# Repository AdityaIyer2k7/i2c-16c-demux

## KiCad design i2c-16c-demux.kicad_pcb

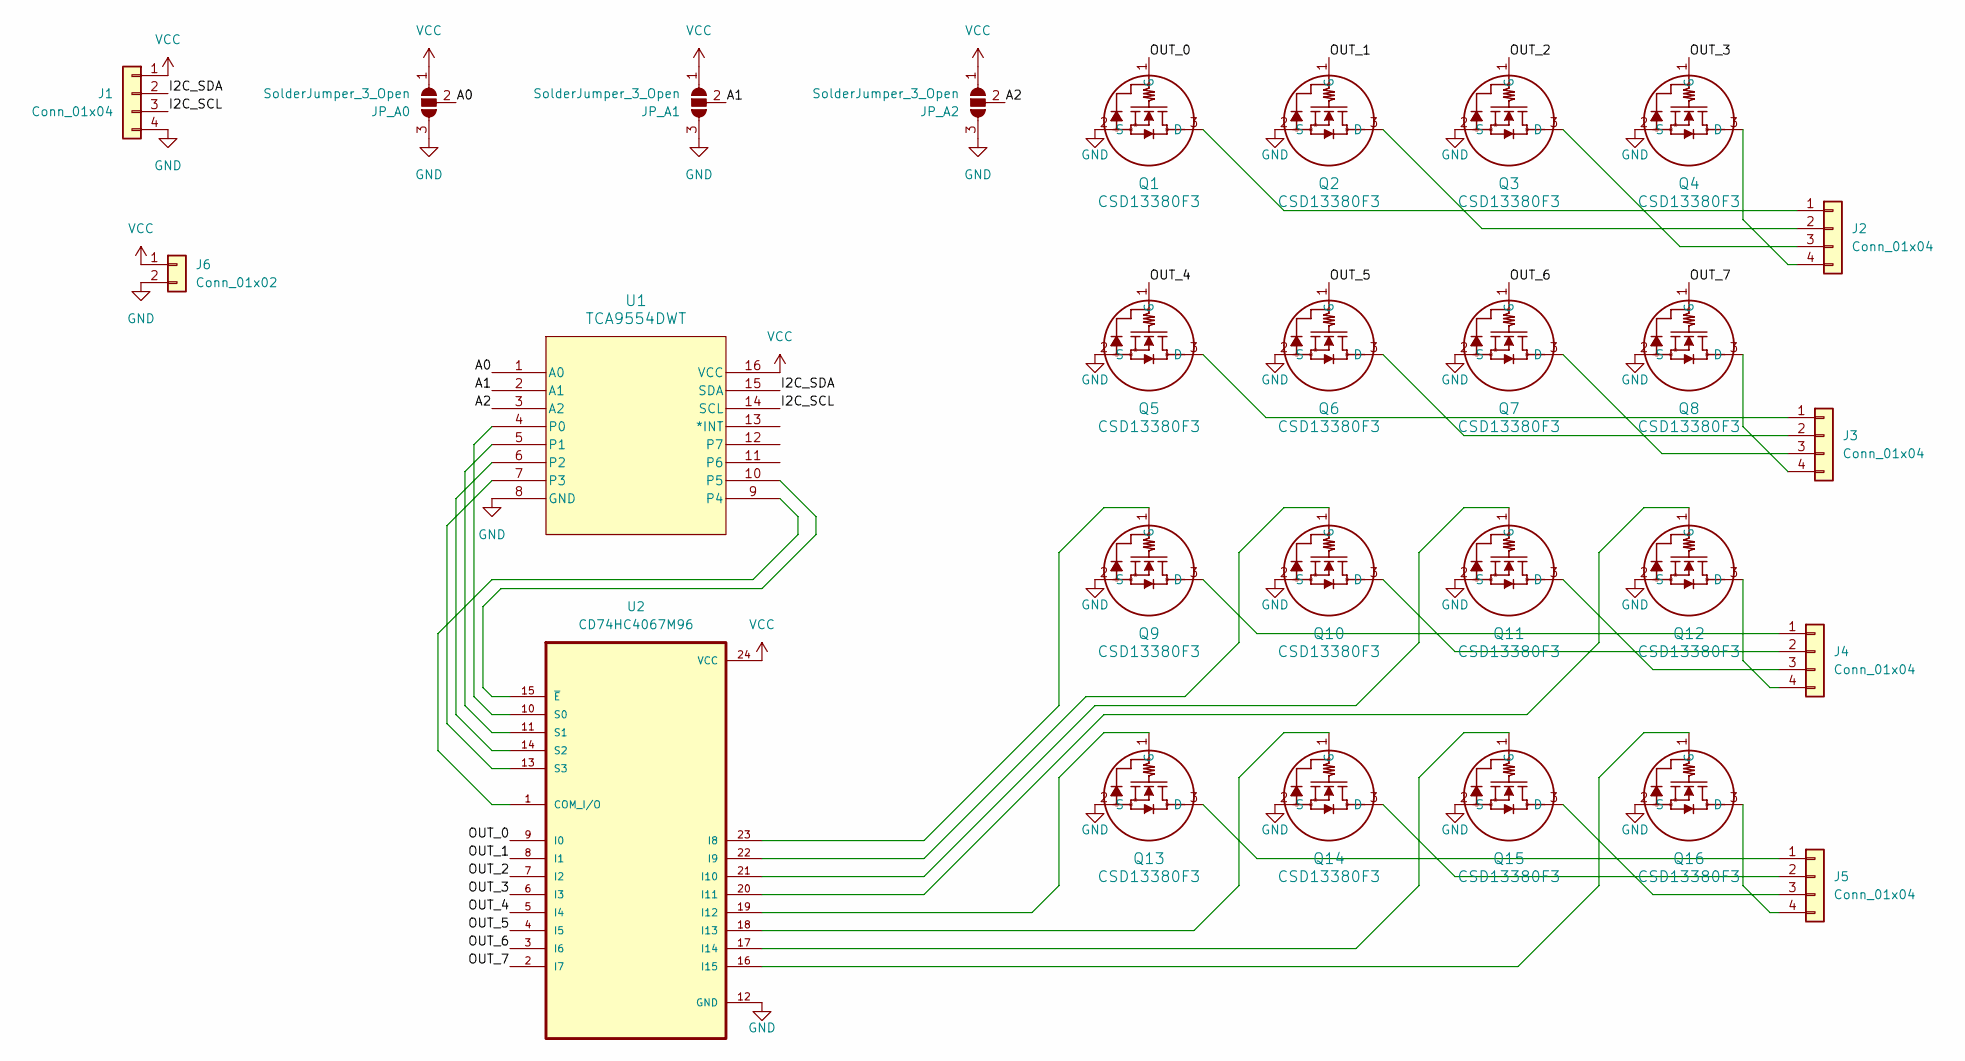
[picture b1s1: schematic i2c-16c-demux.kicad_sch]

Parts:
J1, J2, J3, J4, J5: Conn_01x04; PinSocket_1x04_P2.54mm_Vertical
J6: Conn_01x02; PinSocket_1x02_P2.54mm_Vertical
JP_A0, JP_A1, JP_A2: SolderJumper_3_Open; SolderJumper-3_P2.0mm_Open_TrianglePad1.0x1.5mm
Q1, Q2, Q3, Q4, Q5, Q6, Q7, Q8, Q9, Q10, Q11, Q12, Q13, Q14, Q15, Q16: CSD13380F3; SC59_DIO
U1: TCA9554DWT; PW16_TEX
U2: CD74HC4067M96; SOIC127P1030X265-24N

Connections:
/A0: JP_A0.2 (C), U1.1 (A0)
/A1: JP_A1.2 (C), U1.2 (A1)
/A2: JP_A2.2 (C), U1.3 (A2)
/I2C_SCL: J1.3, U1.14 (SCL)
/I2C_SDA: J1.2, U1.15 (SDA)
/OUT_0: Q1.1 (G), U2.9 (I0)
/OUT_1: Q2.1 (G), U2.8 (I1)
/OUT_2: Q3.1 (G), U2.7 (I2)
/OUT_3: Q4.1 (G), U2.6 (I3)
/OUT_4: Q5.1 (G), U2.5 (I4)
/OUT_5: Q6.1 (G), U2.4 (I5)
/OUT_6: Q7.1 (G), U2.3 (I6)
/OUT_7: Q8.1 (G), U2.2 (I7)
GND: J1.4, J6.2, JP_A0.3 (B), JP_A1.3 (B), JP_A2.3 (B), Q1.2 (S), Q2.2 (S), Q3.2 (S), Q4.2 (S), Q5.2 (S), Q6.2 (S), Q7.2 (S), Q8.2 (S), Q9.2 (S), Q10.2 (S), Q11.2 (S), Q12.2 (S), Q13.2 (S), Q14.2 (S), Q15.2 (S), Q16.2 (S), U1.8 (GND), U2.12 (GND)
unnamed: J2.1, Q1.3 (D)
unnamed: J2.2, Q2.3 (D)
unnamed: J2.3, Q3.3 (D)
unnamed: J2.4, Q4.3 (D)
unnamed: J3.1, Q5.3 (D)
unnamed: J3.2, Q6.3 (D)
unnamed: J3.3, Q7.3 (D)
unnamed: J3.4, Q8.3 (D)
unnamed: J4.1, Q9.3 (D)
unnamed: J4.2, Q10.3 (D)
unnamed: J4.3, Q11.3 (D)
unnamed: J4.4, Q12.3 (D)
unnamed: J5.1, Q13.3 (D)
unnamed: J5.2, Q14.3 (D)
unnamed: J5.3, Q15.3 (D)
unnamed: J5.4, Q16.3 (D)
unnamed: Q9.1 (G), U2.23 (I8)
unnamed: Q10.1 (G), U2.22 (I9)
unnamed: Q11.1 (G), U2.21 (I10)
unnamed: Q12.1 (G), U2.20 (I11)
unnamed: Q13.1 (G), U2.19 (I12)
unnamed: Q14.1 (G), U2.18 (I13)
unnamed: Q15.1 (G), U2.17 (I14)
unnamed: Q16.1 (G), U2.16 (I15)
unnamed: U1.4 (P0), U2.10 (S0)
unnamed: U1.5 (P1), U2.11 (S1)
unnamed: U1.6 (P2), U2.14 (S2)
unnamed: U1.7 (P3), U2.13 (S3)
unnamed: U1.9 (P4), U2.1 (COM_I/O)
unnamed: U1.10 (P5), U2.15 (~E)
VCC: J1.1, J6.1, JP_A0.1 (A), JP_A1.1 (A), JP_A2.1 (A), U1.16 (VCC), U2.24 (VCC)

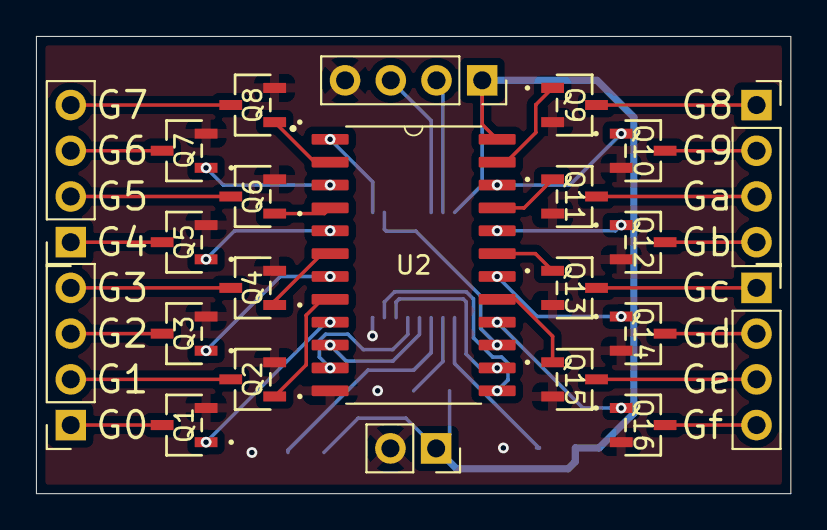
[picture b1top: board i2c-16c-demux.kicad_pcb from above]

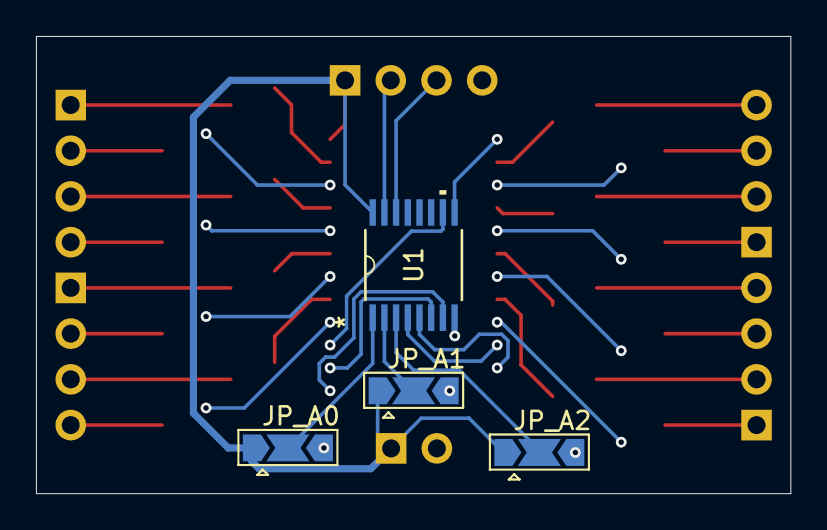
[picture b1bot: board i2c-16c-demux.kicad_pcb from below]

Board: 4 copper layers, 41.9 x 25.4 mm, 27 parts (4 on the bottom side), 45 nets.

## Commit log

2025-12-02 Initial PCB design
2025-12-02 PCB v1.2
2025-12-02 Change gitignore
2025-12-02 Changed fp
